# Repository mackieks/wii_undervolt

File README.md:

Adjustable regulator board for Wii undervolting testing and current measurement. Solderpad Hardware License v2.1 

- 3.5 - 5.5V input
- x4 MUN3CAD03-SE 0.6-3.3V 3A buck regulators
- Trimpots for output voltage adjustment (feedback resistors pre-tuned for Wii undervolting)
- 4-terminal current sense resistors for input and outputs
- [Mouser project with BOM
](https://www.mouser.com/ProjectManager/ProjectDetail.aspx?AccessID=8f9d8d9514)

Vin and each regulator output have dedicated 100-milliohm 4-terminal sense resistors. When powering a load from the reg board, you can measure across the resistors by poking your multimeter probes into the plated test pads. Multiply the voltage by 10 to get the load current in amps.

Each regulator has a trimpot for adjusting the voltage. Turn it clockwise to increase Vout, and counterclockwise to decrease Vout. You can turn the pots with tweezers or a tiny, blunt Phillips screwdriver. The Vout ranges are bounded by resistors so that the entire pot range is usable (and to avoid pumping 5v into any of the rails.)

**Note:** the trimpots are fragile mechanical devices. If you turn them too far in one direction, they'll 'wrap around' to the other side. When overturned like this, there's a small region that won't produce a reasonable resistance, causing Vout to collapse. Just keep turning and Vout will jump back to the intended range.

## Schematic

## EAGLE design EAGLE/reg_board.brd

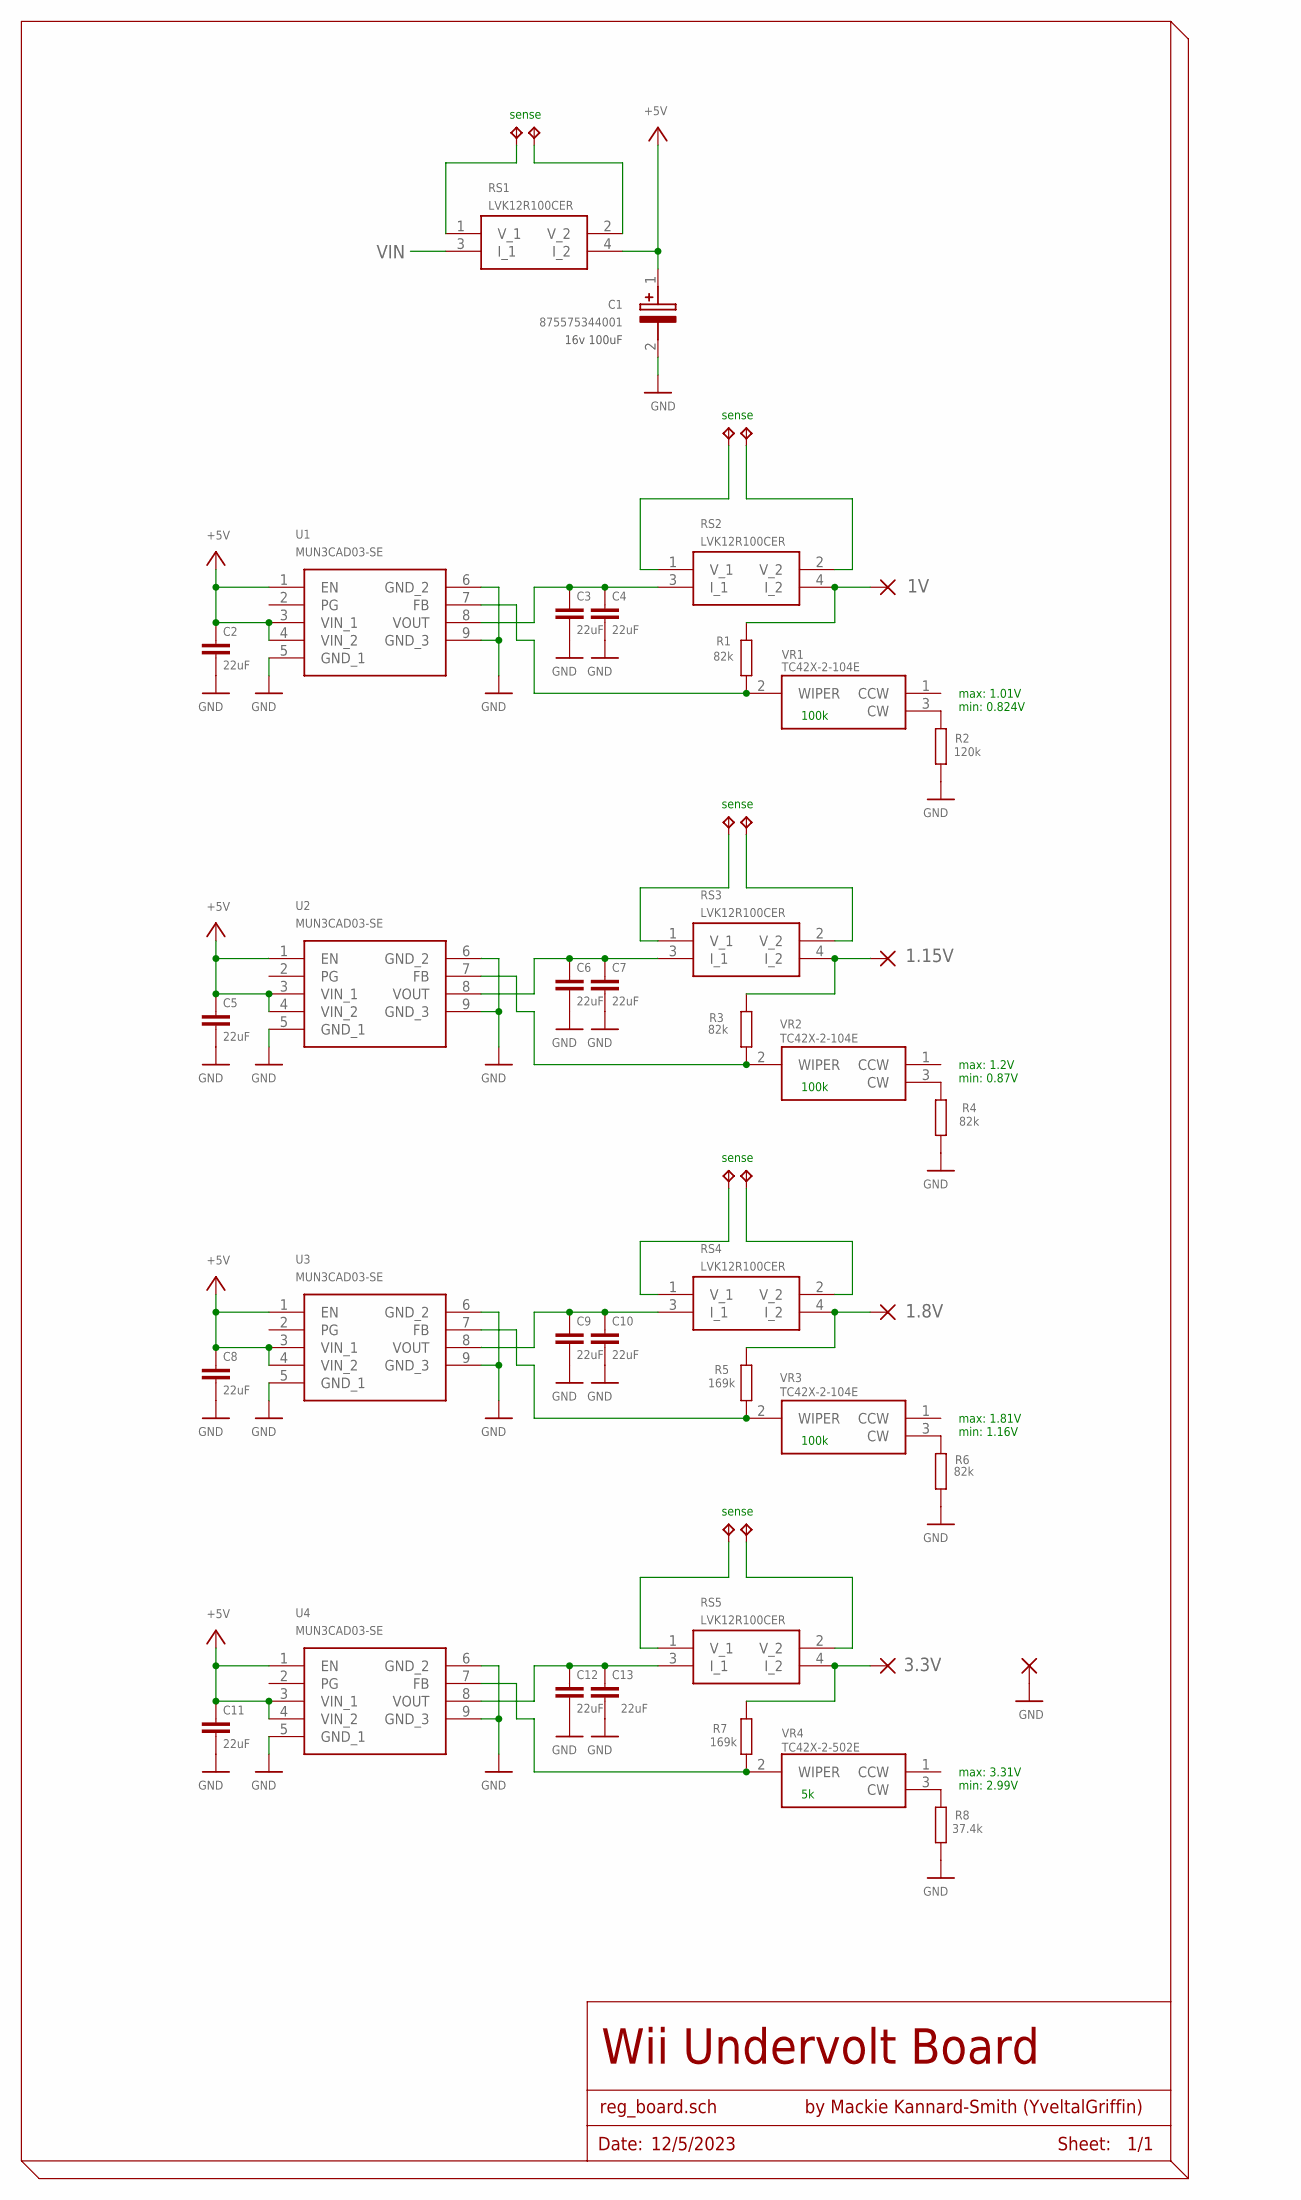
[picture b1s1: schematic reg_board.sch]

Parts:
C1: 875575344001; CAPAE660X610N
C2, C3, C4, C5, C6, C7, C8, C9, C10, C11, C12, C13: 22uF; C0603
PAD1, PAD2, PAD3, PAD4, PAD5: SMD5; SMD2,54-5,08
R1, R3, R4, R6: 82k; R0402
R2: 120k; R0402
R5, R7: 169k; R0402
R8: 37.4k; R0402
RS1, RS2, RS3, RS4, RS5: LVK12R100CER
TP1, TP2, TP3, TP4, TP5, TP6, TP7, TP8, TP9, TP10: TPTP08R; TP08R
U1, U2, U3, U4: MUN3CAD03-SE; MUN3CAD03SE
VR1, VR2, VR3: TC42X-2-104E; TC42X2103E
VR4: TC42X-2-502E; TC42X2103E

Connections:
1.8V: PAD4.1, R5.2, RS4.4 (I_2)
1.15V: PAD3.1, R3.2, RS3.4 (I_2)
1V: PAD1.1, R1.2, RS2.4 (I_2)
3.3V: PAD5.1, R7.2, RS5.4 (I_2)
+5V: C1.1 (+), C2.1, C5.1, C8.1, C11.1, RS1.4 (I_2), U1.1 (EN), U1.3 (VIN_1), U1.4 (VIN_2), U2.1 (EN), U2.3 (VIN_1), U2.4 (VIN_2), U3.1 (EN), U3.3 (VIN_1), U3.4 (VIN_2), U4.1 (EN), U4.3 (VIN_1), U4.4 (VIN_2)
GND: C1.2 (-), C2.2, C3.2, C4.2, C5.2, C6.2, C7.2, C8.2, C9.2, C10.2, C11.2, C12.2, C13.2, PAD2.1, R2.1, R4.1, R6.1, R8.1, U1.5 (GND_1), U1.6 (GND_2), U1.9 (GND_3), U2.5 (GND_1), U2.6 (GND_2), U2.9 (GND_3), U3.5 (GND_1), U3.6 (GND_2), U3.9 (GND_3), U4.5 (GND_1), U4.6 (GND_2), U4.9 (GND_3)
unnamed: R2.2, VR1.3 (CW)
unnamed: R4.2, VR2.3 (CW)
unnamed: R1.1, U1.7 (FB), VR1.2 (WIPER)
unnamed: RS2.1 (V_1), TP1.TP
unnamed: RS2.2 (V_2), TP2.TP
unnamed: R6.2, VR3.3 (CW)
unnamed: RS1.2 (V_2), TP3.TP
unnamed: RS1.1 (V_1), TP4.TP
unnamed: R3.1, U2.7 (FB), VR2.2 (WIPER)
unnamed: RS3.1 (V_1), TP5.TP
unnamed: RS3.2 (V_2), TP6.TP
unnamed: R5.1, U3.7 (FB), VR3.2 (WIPER)
unnamed: RS4.1 (V_1), TP7.TP
unnamed: RS4.2 (V_2), TP8.TP
unnamed: R7.1, U4.7 (FB), VR4.2 (WIPER)
unnamed: RS5.1 (V_1), TP9.TP
unnamed: RS5.2 (V_2), TP10.TP
unnamed: R8.2, VR4.3 (CW)
VIN: RS1.3 (I_1)
VOUT1: C3.1, C4.1, RS2.3 (I_1), U1.8 (VOUT)
VOUT2: C6.1, C7.1, RS3.3 (I_1), U2.8 (VOUT)
VOUT3: C9.1, C10.1, RS4.3 (I_1), U3.8 (VOUT)
VOUT4: C12.1, C13.1, RS5.3 (I_1), U4.8 (VOUT)

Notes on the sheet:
100k
max: 1.01V min: 0.824V
max: 1.2V min: 0.87V
max: 1.81V min: 1.16V
max: 3.31V min: 2.99V
16v 100uF
sense
Wii Undervolt Board
reg_board.sch
by Mackie Kannard-Smith (YveltalGriffin)
Date:
12/5/2023
Sheet: 1/1

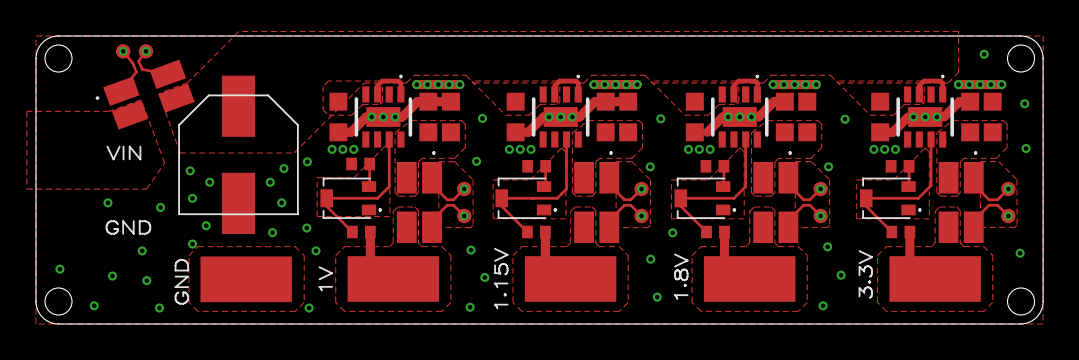
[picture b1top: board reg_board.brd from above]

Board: 2 copper layers, 56.0 x 16.0 mm, 49 parts (0 on the bottom side), 28 nets.

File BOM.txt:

Partlist

Exported from reg_board.sch at 1/16/2024 12:08 PM

EAGLE Version 9.6.2 Copyright (c) 1988-2020 Autodesk, Inc.

Assembly variant: 

Part     Value          Device       Package       Library        Sheet

C1       875575344001   875575344001 CAPAE660X610N SamacSys_Parts 1
C2       22uF           C-USC0603    C0603         resistor       1
C3       22uF           C-USC0603    C0603         resistor       1
C4       22uF           C-USC0603    C0603         resistor       1
C5       22uF           C-USC0603    C0603         resistor       1
C6       22uF           C-USC0603    C0603         resistor       1
C7       22uF           C-USC0603    C0603         resistor       1
C8       22uF           C-USC0603    C0603         resistor       1
C9       22uF           C-USC0603    C0603         resistor       1
C10      22uF           C-USC0603    C0603         resistor       1
C11      22uF           C-USC0603    C0603         resistor       1
C12      22uF           C-USC0603    C0603         resistor       1
C13      22uF           C-USC0603    C0603         resistor       1
PAD1                    SMD5         SMD2,54-5,08  wirepad        1
PAD2                    SMD5         SMD2,54-5,08  wirepad        1
PAD3                    SMD5         SMD2,54-5,08  wirepad        1
PAD4                    SMD5         SMD2,54-5,08  wirepad        1
PAD5                    SMD5         SMD2,54-5,08  wirepad        1
R1       82k            R-US_R0402   R0402         resistor       1
R2       120k           R-US_R0402   R0402         resistor       1
R3       82k            R-US_R0402   R0402         resistor       1
R4       82k            R-US_R0402   R0402         resistor       1
R5       169k           R-US_R0402   R0402         resistor       1
R6       82k            R-US_R0402   R0402         resistor       1
R7       169k           R-US_R0402   R0402         resistor       1
R8       37.4k          R-US_R0402   R0402         resistor       1
RS1      LVK12R100CER   LVK12R100CER LVK12R100CER  SamacSys_Parts 1
RS2      LVK12R100CER   LVK12R100CER LVK12R100CER  SamacSys_Parts 1
RS3      LVK12R100CER   LVK12R100CER LVK12R100CER  SamacSys_Parts 1
RS4      LVK12R100CER   LVK12R100CER LVK12R100CER  SamacSys_Parts 1
RS5      LVK12R100CER   LVK12R100CER LVK12R100CER  SamacSys_Parts 1
TP1      TPTP08R        TPTP08R      TP08R         testpad        1
TP2      TPTP08R        TPTP08R      TP08R         testpad        1
TP3      TPTP08R        TPTP08R      TP08R         testpad        1
TP4      TPTP08R        TPTP08R      TP08R         testpad        1
TP5      TPTP08R        TPTP08R      TP08R         testpad        1
TP6      TPTP08R        TPTP08R      TP08R         testpad        1
TP7      TPTP08R        TPTP08R      TP08R         testpad        1
TP8      TPTP08R        TPTP08R      TP08R         testpad        1
TP9      TPTP08R        TPTP08R      TP08R         testpad        1
TP10     TPTP08R        TPTP08R      TP08R         testpad        1
U1       MUN3CAD03-SE   MUN3CAD03-SE MUN3CAD03SE   SamacSys_Parts 1
U2       MUN3CAD03-SE   MUN3CAD03-SE MUN3CAD03SE   SamacSys_Parts 1
U3       MUN3CAD03-SE   MUN3CAD03-SE MUN3CAD03SE   SamacSys_Parts 1
U4       MUN3CAD03-SE   MUN3CAD03-SE MUN3CAD03SE   SamacSys_Parts 1
VR1      TC42X-2-104E   TC42X-2-104E TC42X2103E    SamacSys_Parts 1
VR2      TC42X-2-104E   TC42X-2-104E TC42X2103E    SamacSys_Parts 1
VR3      TC42X-2-104E   TC42X-2-104E TC42X2103E    SamacSys_Parts 1
VR4      TC42X-2-502E   TC42X-2-104E TC42X2103E    SamacSys_Parts 1

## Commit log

2024-01-16 push design
2024-04-22 update iBOM
